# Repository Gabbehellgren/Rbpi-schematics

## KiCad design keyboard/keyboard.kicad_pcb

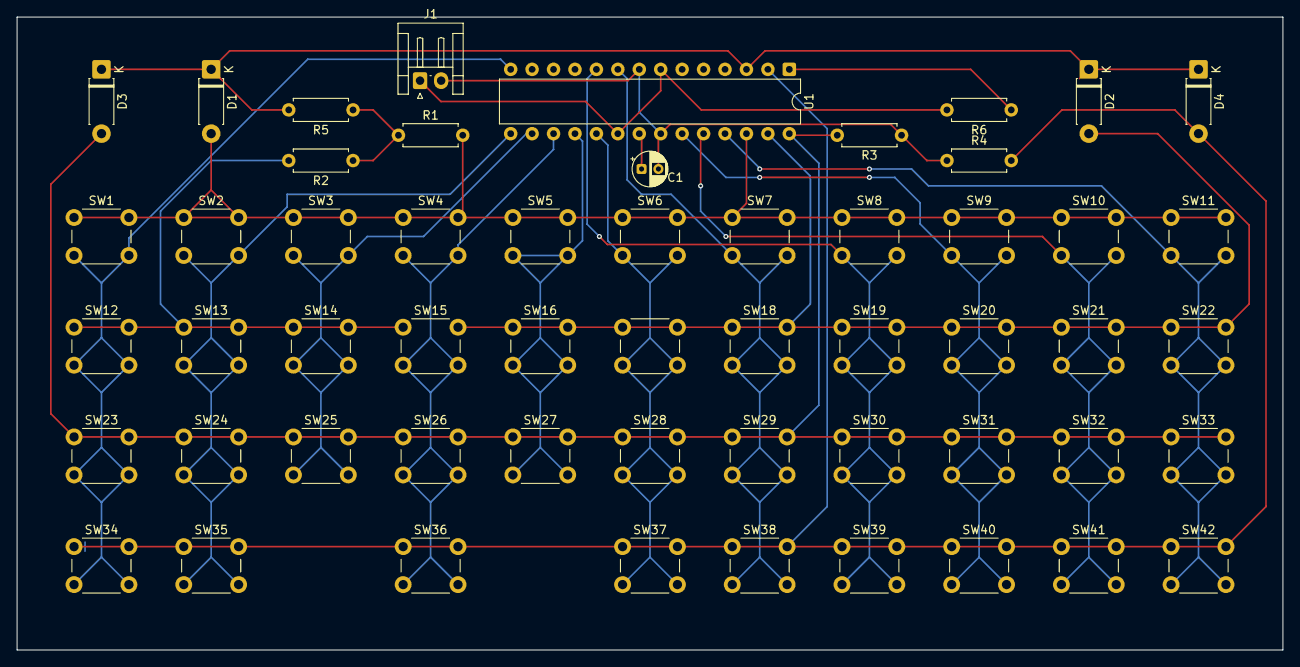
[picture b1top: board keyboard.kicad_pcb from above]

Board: 2 copper layers, 150.0 x 75.0 mm, 55 parts (0 on the bottom side), 20 nets.

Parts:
C1: C; CP_Radial_D4.0mm_P2.00mm
D1, D2, D3, D4: D; D_DO-41_SOD81_P7.62mm_Horizontal
J1: Conn_01x02_Socket; JST_EH_S2B-EH_1x02_P2.50mm_Horizontal
R1, R2, R3, R4, R5, R6: 10k; R_Axial_DIN0207_L6.3mm_D2.5mm_P7.62mm_Horizontal
SW1, SW2, SW3, SW4, SW5, SW6, SW7, SW8, SW9, SW10, SW11, SW12, SW13, SW14, SW15, SW16, SW17, SW18, SW19, SW20, SW21, SW22, SW23, SW24, SW25, SW26, SW27, SW28, SW29, SW30, SW31, SW32, SW33, SW34, SW35, SW36, SW37, SW38, SW39, SW40, SW41, SW42: SW_Push; SW_PUSH_6mm_H4.3mm
U1: ATmega48-20P; DIP-28_W7.62mm

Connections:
+5V: J1.1, R6.2, U1.7 (VCC), U1.20 (AVCC)
/COL1: SW1.2, SW12.2, SW23.2, SW34.2, U1.14 (PB0)
/COL2: SW2.2, SW13.2, SW24.2, SW35.2, U1.15 (PB1)
/COL3: SW3.2, SW14.2, SW25.2, U1.16 (PB2)
/COL4: SW4.2, SW15.2, SW26.2, SW36.2, U1.17 (PB3)
/COL5: SW5.2, SW16.2, SW27.2, U1.18 (PB4)
/COL6: SW6.2, SW17.2, SW28.2, SW37.2, U1.19 (PB5)
/COL7: SW7.2, SW18.2, SW29.2, SW38.2, U1.9 (XTAL1/PB6)
/COL8: SW8.2, SW19.2, SW30.2, SW39.2, U1.10 (XTAL2/PB7)
/COL9: SW9.2, SW20.2, SW31.2, SW40.2, U1.23 (PC0)
/COL10: SW10.2, SW21.2, SW32.2, SW41.2, U1.24 (PC1)
/COL11: SW11.2, SW22.2, SW33.2, SW42.2, U1.25 (PC2)
/ROW1: D1.2 (A), R1.2, SW1.1, SW2.1, SW3.1, SW4.1, SW5.1, SW6.1, SW7.1, SW8.1, SW9.1, SW10.1, SW11.1, U1.26 (PC3)
/ROW2: D2.2 (A), R2.2, SW12.1, SW13.1, SW14.1, SW15.1, SW16.1, SW17.1, SW18.1, SW19.1, SW20.1, SW21.1, SW22.1, U1.27 (PC4)
/ROW3: D3.2 (A), R3.2, SW23.1, SW24.1, SW25.1, SW26.1, SW27.1, SW28.1, SW29.1, SW30.1, SW31.1, SW32.1, SW33.1, U1.28 (PC5)
/ROW4: D4.2 (A), R4.2, SW34.1, SW35.1, SW36.1, SW37.1, SW38.1, SW39.1, SW40.1, SW41.1, SW42.1, U1.2 (PD0)
/Trigger: D1.1 (K), D2.1 (K), D3.1 (K), D4.1 (K), R5.2, U1.3 (PD1)
GND: C1.2, J1.2, R1.1, R2.1, R3.1, R4.1, R5.1, U1.8 (GND), U1.22 (GND)
unnamed: C1.1, U1.21 (AREF)
unnamed: R6.1, U1.1 (~RESET/PC6)
